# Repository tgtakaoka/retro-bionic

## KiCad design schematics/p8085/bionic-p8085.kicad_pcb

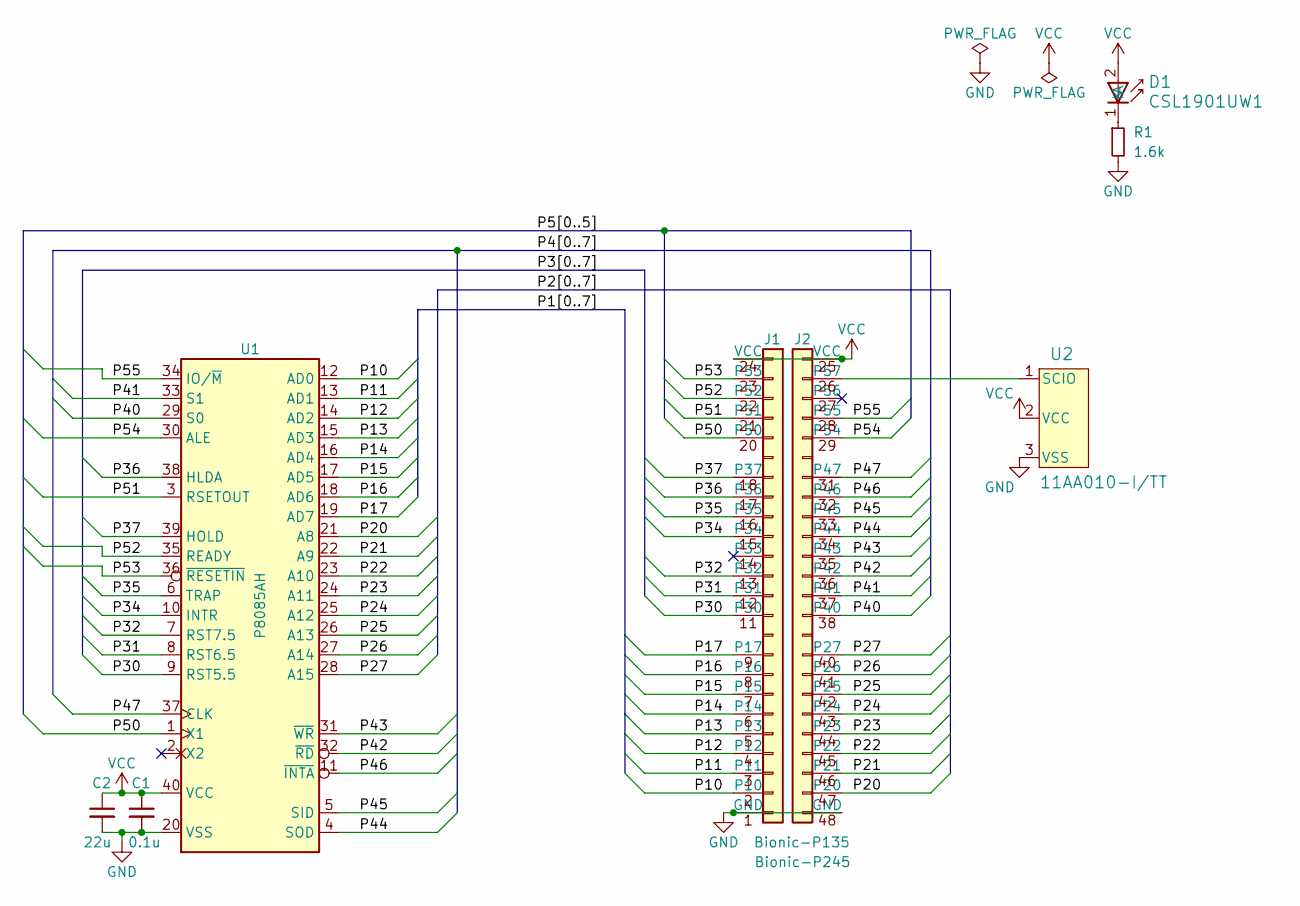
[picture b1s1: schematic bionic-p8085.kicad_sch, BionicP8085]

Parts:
C1: 0.1u; C_0603_1608Metric_Pad1.08x0.95mm_HandSolder
C2: 22u; C_0603_1608Metric_Pad1.08x0.95mm_HandSolder
D1: CSL1901UW1; LED_CSL1901UW1_ROM-M
J1: Bionic-P135; Bionic-P135_THT
J2: Bionic-P245; Bionic-P245_THT
R1: 1.6k; R_0603_1608Metric_Pad0.98x0.95mm_HandSolder
U1: P8085AH; DIP-40_W15.24mm_Socket
U2: 11AA010-I/TT; SOT-23_MC_MCH-M

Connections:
/P10: J1.2 (P10), U1.12 (AD0)
/P11: J1.3 (P11), U1.13 (AD1)
/P12: J1.4 (P12), U1.14 (AD2)
/P13: J1.5 (P13), U1.15 (AD3)
/P14: J1.6 (P14), U1.16 (AD4)
/P15: J1.7 (P15), U1.17 (AD5)
/P16: J1.8 (P16), U1.18 (AD6)
/P17: J1.9 (P17), U1.19 (AD7)
/P20: J2.47 (P20), U1.21 (A8)
/P21: J2.46 (P21), U1.22 (A9)
/P22: J2.45 (P22), U1.23 (A10)
/P23: J2.44 (P23), U1.24 (A11)
/P24: J2.43 (P24), U1.25 (A12)
/P25: J2.42 (P25), U1.26 (A13)
/P26: J2.41 (P26), U1.27 (A14)
/P27: J2.40 (P27), U1.28 (A15)
/P30: J1.11 (P30), U1.9 (RST5.5)
/P31: J1.12 (P31), U1.8 (RST6.5)
/P32: J1.13 (P32), U1.7 (RST7.5)
/P34: J1.15 (P34), U1.10 (INTR)
/P35: J1.16 (P35), U1.6 (TRAP)
/P36: J1.17 (P36), U1.38 (HLDA)
/P37: J1.18 (P37), U1.39 (HOLD)
/P40: J2.38 (P40), U1.29 (S0)
/P41: J2.37 (P41), U1.33 (S1)
/P42: J2.36 (P42), U1.32 (~RD)
/P43: J2.35 (P43), U1.31 (~WR)
/P44: J2.34 (P44), U1.4 (SOD)
/P45: J2.33 (P45), U1.5 (SID)
/P46: J2.32 (P46), U1.11 (~INTA)
/P47: J2.31 (P47), U1.37 (CLK)
/P50: J1.20 (P50), U1.1 (X1)
/P51: J1.21 (P51), U1.3 (RSETOUT)
/P52: J1.22 (P52), U1.35 (READY)
/P53: J1.23 (P53), U1.36 (~RESETIN)
/P54: J2.29 (P54), U1.30 (ALE)
/P55: J2.28 (P55), U1.34 (IO/~M)
GND: C1.2, C2.2, J1.1 (GND), J2.48 (GND), R1.2, U1.20 (VSS), U2.3 (VSS)
unnamed: D1.1 (K), R1.1
unnamed: J2.26 (P57), U2.1 (SCIO)
VCC: C1.1, C2.1, D1.2 (A), J1.24 (VCC), J2.25 (VCC), U1.40 (VCC), U2.2 (VCC)

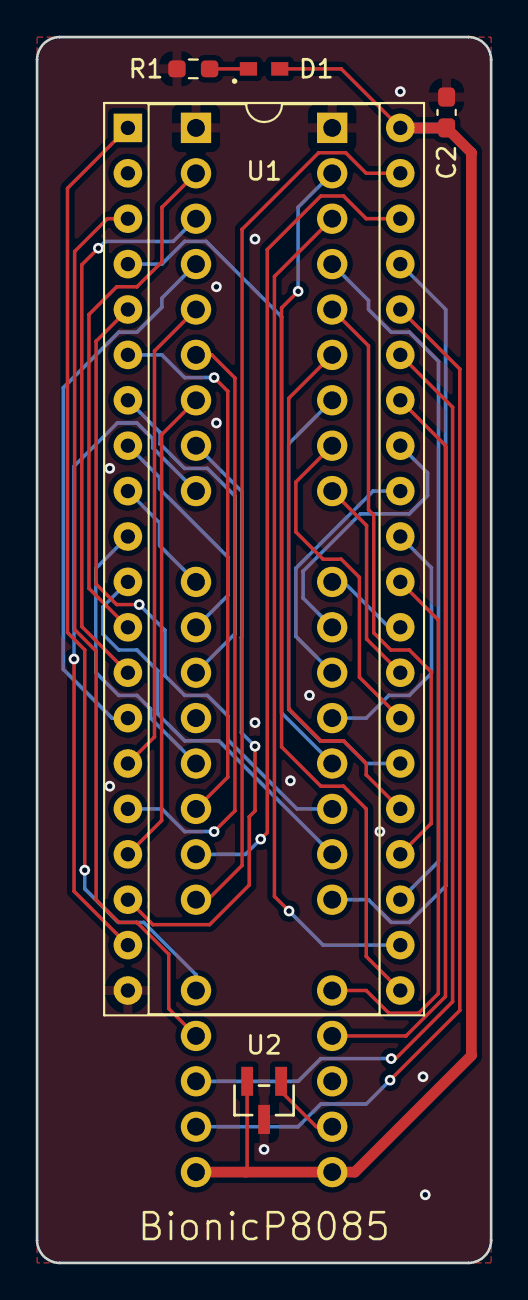
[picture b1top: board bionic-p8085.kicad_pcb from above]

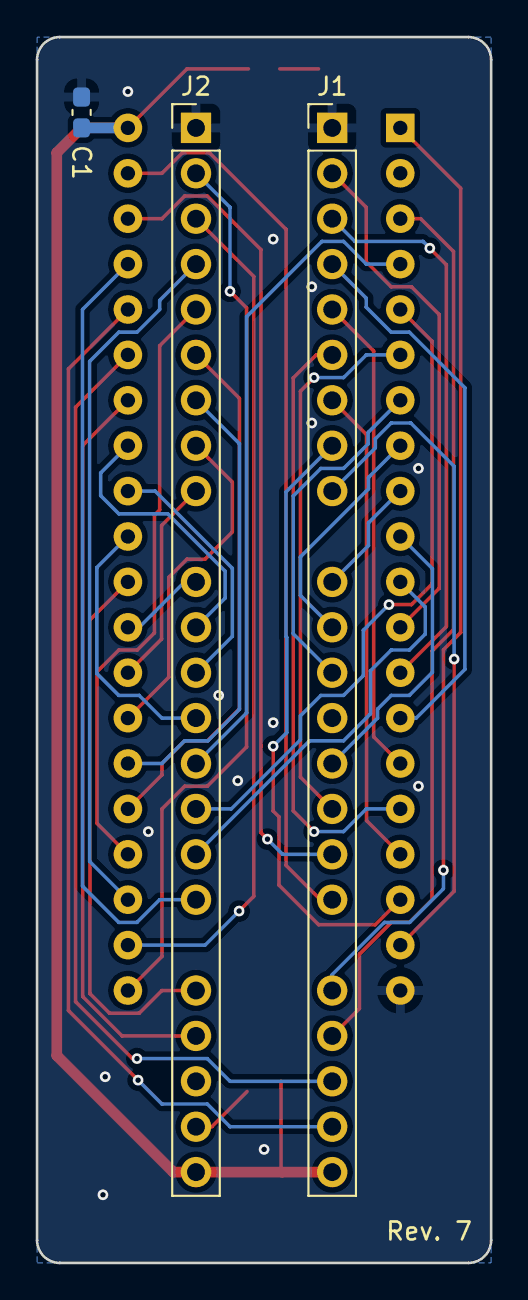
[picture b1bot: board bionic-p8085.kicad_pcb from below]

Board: 2 copper layers, 25.4 x 68.6 mm, 8 parts (3 on the bottom side), 41 nets.

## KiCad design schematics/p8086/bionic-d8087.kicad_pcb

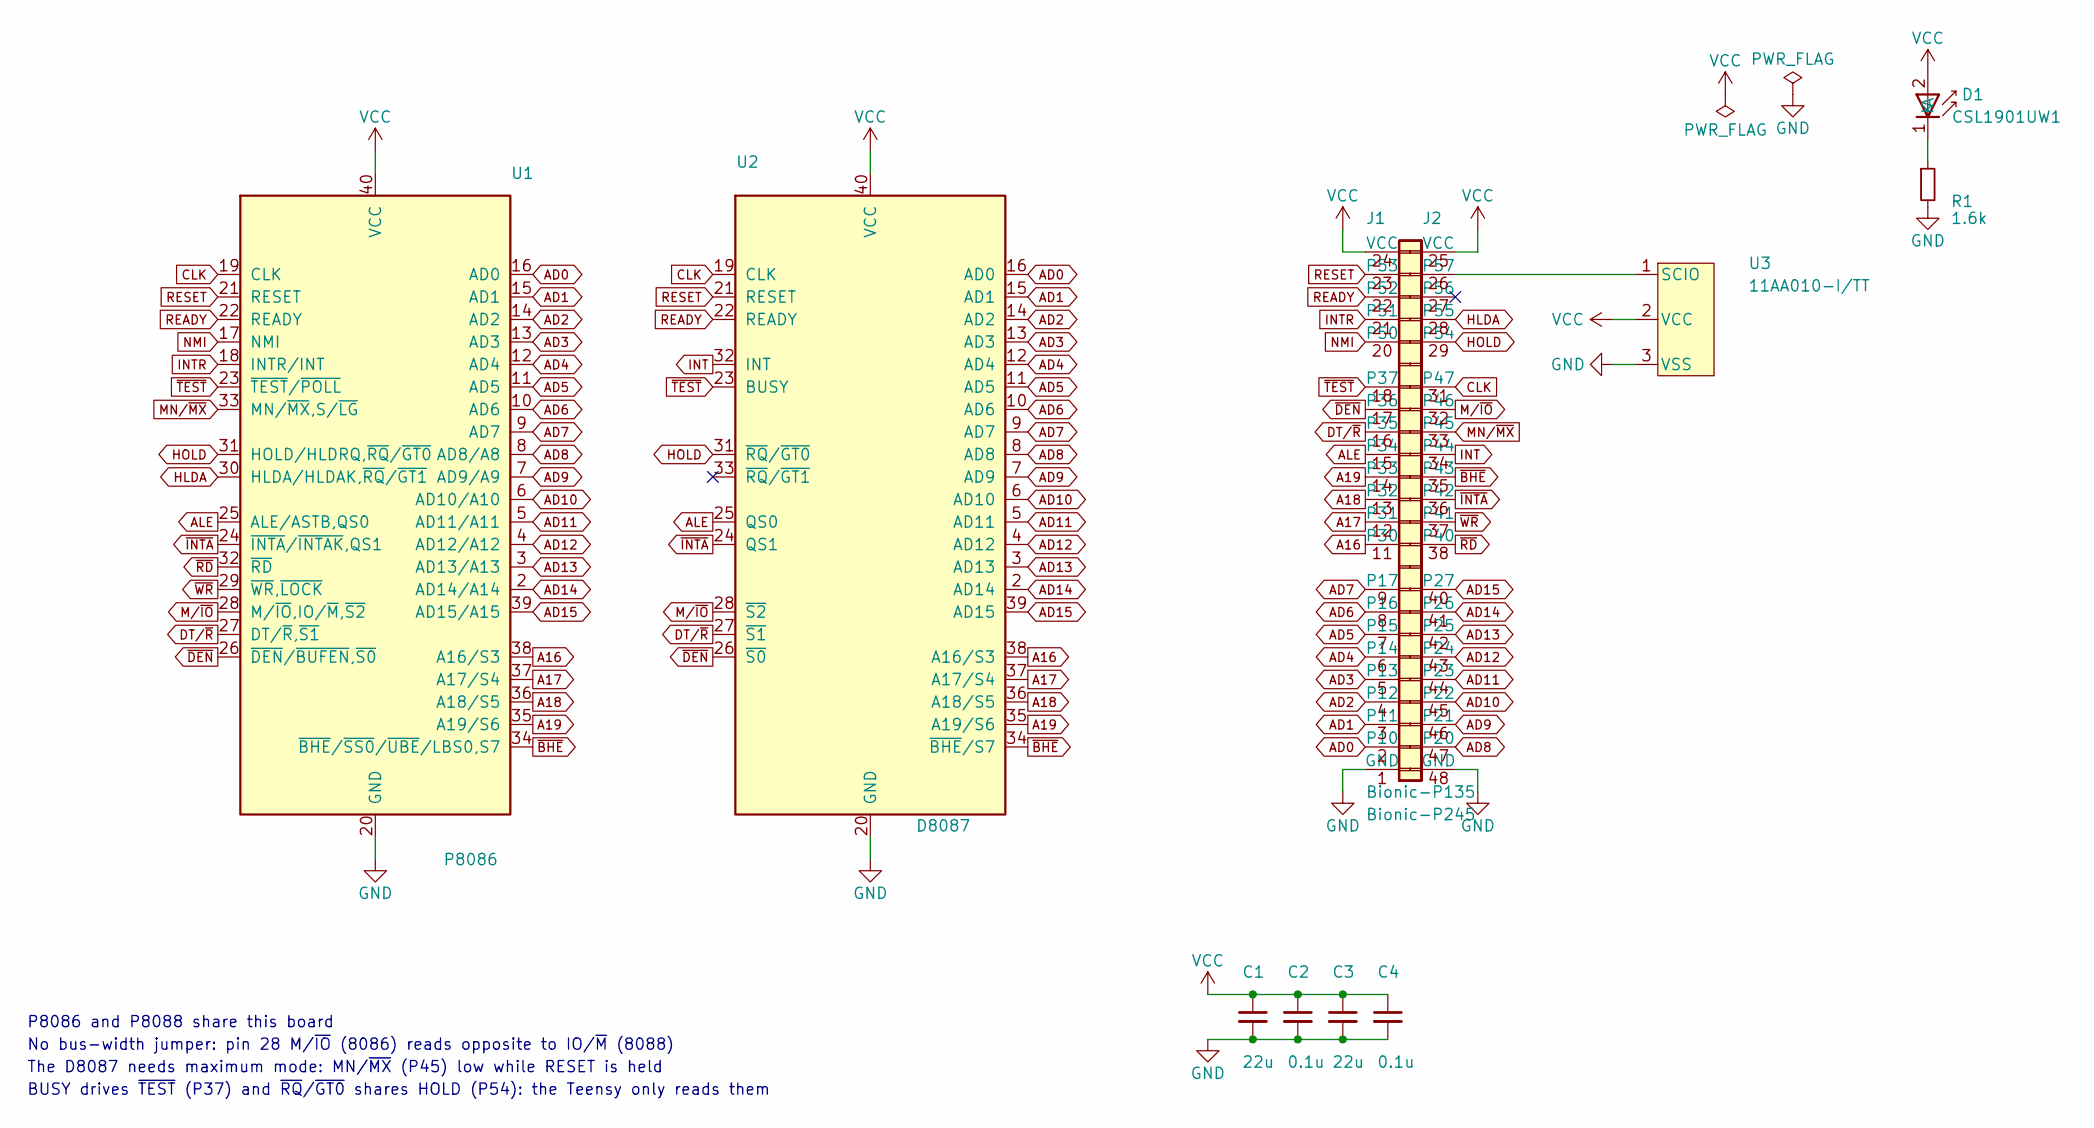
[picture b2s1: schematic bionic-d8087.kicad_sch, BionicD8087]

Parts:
C1, C3: 22u; C_0603_1608Metric_Pad1.08x0.95mm_HandSolder
C2, C4: 0.1u; C_0603_1608Metric_Pad1.08x0.95mm_HandSolder
D1: CSL1901UW1; LED_CSL1901UW1_ROM-M
J1: Bionic-P135; Bionic-P135_THT
J2: Bionic-P245; Bionic-P245_THT
R1: 1.6k; R_0603_1608Metric_Pad0.98x0.95mm_HandSolder
U1: P8086; DIP-40_W15.24mm_Socket
U2: D8087; DIP-40_W15.24mm_Socket
U3: 11AA010-I/TT; SOT-23_MC_MCH-M

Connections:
A16: J1.11 (P30), U1.38 (A16/S3), U2.38 (A16/S3)
A17: J1.12 (P31), U1.37 (A17/S4), U2.37 (A17/S4)
A18: J1.13 (P32), U1.36 (A18/S5), U2.36 (A18/S5)
A19: J1.14 (P33), U1.35 (A19/S6), U2.35 (A19/S6)
AD0: J1.2 (P10), U1.16 (AD0), U2.16 (AD0)
AD1: J1.3 (P11), U1.15 (AD1), U2.15 (AD1)
AD2: J1.4 (P12), U1.14 (AD2), U2.14 (AD2)
AD3: J1.5 (P13), U1.13 (AD3), U2.13 (AD3)
AD4: J1.6 (P14), U1.12 (AD4), U2.12 (AD4)
AD5: J1.7 (P15), U1.11 (AD5), U2.11 (AD5)
AD6: J1.8 (P16), U1.10 (AD6), U2.10 (AD6)
AD7: J1.9 (P17), U1.9 (AD7), U2.9 (AD7)
AD8: J2.47 (P20), U1.8 (AD8/A8), U2.8 (AD8)
AD9: J2.46 (P21), U1.7 (AD9/A9), U2.7 (AD9)
AD10: J2.45 (P22), U1.6 (AD10/A10), U2.6 (AD10)
AD11: J2.44 (P23), U1.5 (AD11/A11), U2.5 (AD11)
AD12: J2.43 (P24), U1.4 (AD12/A12), U2.4 (AD12)
AD13: J2.42 (P25), U1.3 (AD13/A13), U2.3 (AD13)
AD14: J2.41 (P26), U1.2 (AD14/A14), U2.2 (AD14)
AD15: J2.40 (P27), U1.39 (AD15/A15), U2.39 (AD15)
ALE: J1.15 (P34), U1.25 (ALE/ASTB,QS0), U2.25 (QS0)
CLK: J2.31 (P47), U1.19 (CLK), U2.19 (CLK)
DT/~R: J1.16 (P35), U1.27 (DT/~R,~S1), U2.27 (~S1)
GND: C1.2, C2.2, C3.2, C4.2, J1.1 (GND), J2.48 (GND), R1.2, U1.1 (GND), U1.20 (GND), U2.1 (GND), U2.20 (GND), U3.3 (VSS)
HLDA: J2.28 (P55), U1.30 (HLDA/HLDAK,~RQ/~GT1)
HOLD: J2.29 (P54), U1.31 (HOLD/HLDRQ,~RQ/~GT0), U2.31 (~RQ/~GT0)
INT: J2.34 (P44), U2.32 (INT)
INTR: J1.21 (P51), U1.18 (INTR/INT)
MN/~MX: J2.33 (P45), U1.33 (MN/~MX,S/~LG)
M/~IO: J2.32 (P46), U1.28 (M/~IO,IO/~M,~S2), U2.28 (~S2)
NMI: J1.20 (P50), U1.17 (NMI)
unnamed: D1.1 (K), R1.1
unnamed: J2.26 (P57), U3.1 (SCIO)
READY: J1.22 (P52), U1.22 (READY), U2.22 (READY)
RESET: J1.23 (P53), U1.21 (RESET), U2.21 (RESET)
VCC: C1.1, C2.1, C3.1, C4.1, D1.2 (A), J1.24 (VCC), J2.25 (VCC), U1.40 (VCC), U2.40 (VCC), U3.2 (VCC)
~BHE: J2.35 (P43), U1.34 (~BHE/~SS0/~UBE/LBS0,S7), U2.34 (~BHE/S7)
~DEN: J1.17 (P36), U1.26 (~DEN/~BUFEN,~S0), U2.26 (~S0)
~INTA: J2.36 (P42), U1.24 (~INTA/~INTAK,QS1), U2.24 (QS1)
~RD: J2.38 (P40), U1.32 (~RD)
~TEST: J1.18 (P37), U1.23 (~TEST/~POLL), U2.23 (BUSY)
~WR: J2.37 (P41), U1.29 (~WR,~LOCK)

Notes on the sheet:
P8086 and P8088 share this board
The D8087 needs maximum mode: MN/~{MX} (P45) low while RESET is held
No bus-width jumper: pin 28 M/~{IO} (8086) reads opposite to IO/~{M} (8088)
BUSY drives ~{TEST} (P37) and ~{RQ}/~{GT0} shares HOLD (P54): the Teensy only reads them

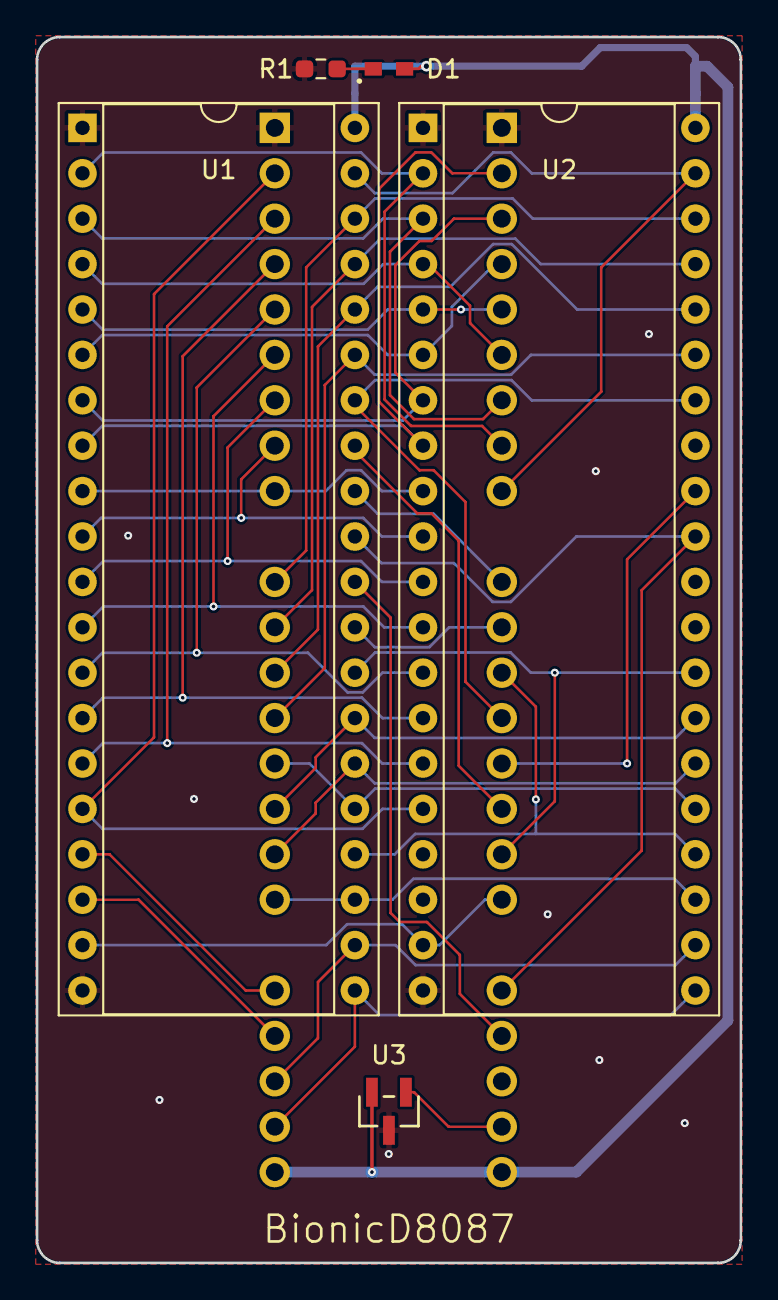
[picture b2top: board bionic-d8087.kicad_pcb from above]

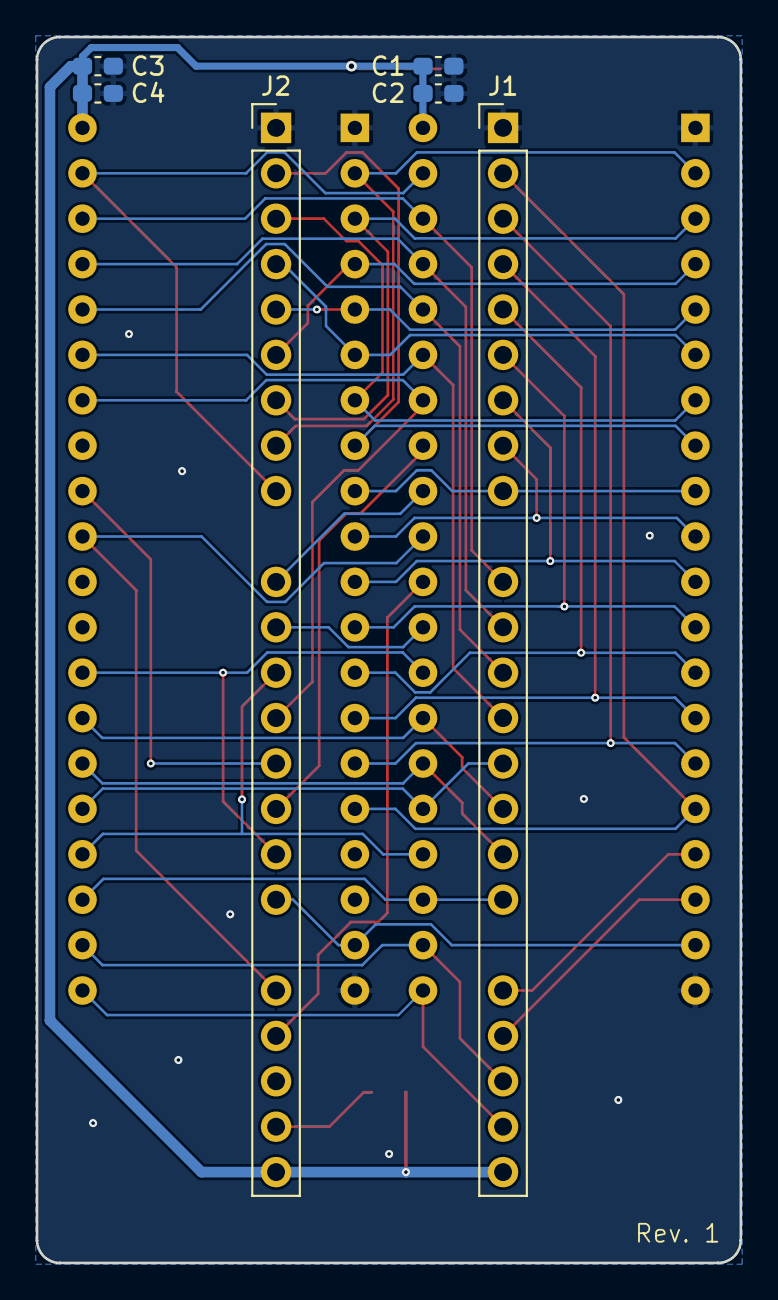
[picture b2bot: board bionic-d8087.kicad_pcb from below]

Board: 2 copper layers, 39.4 x 68.6 mm, 11 parts (6 on the bottom side), 42 nets.

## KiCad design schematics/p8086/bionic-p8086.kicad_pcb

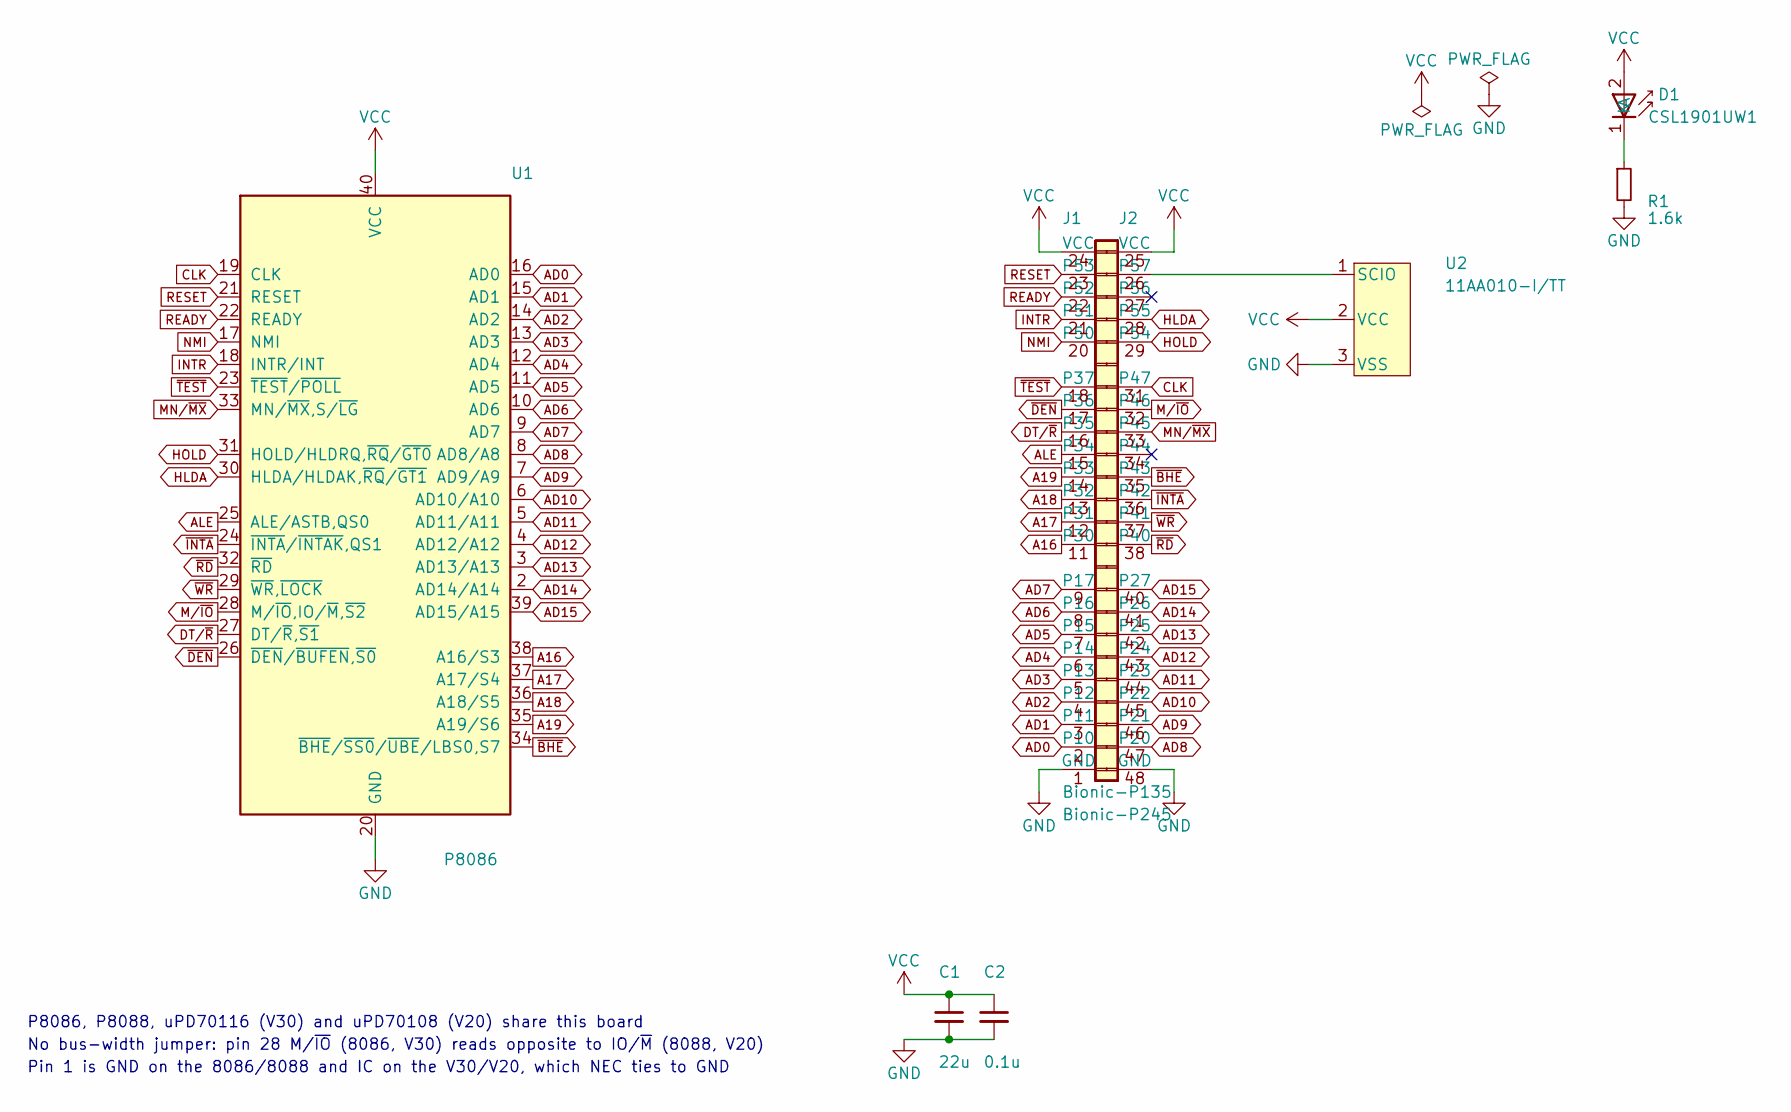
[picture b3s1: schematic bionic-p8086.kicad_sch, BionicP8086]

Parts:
C1: 22u; C_0603_1608Metric_Pad1.08x0.95mm_HandSolder
C2: 0.1u; C_0603_1608Metric_Pad1.08x0.95mm_HandSolder
D1: CSL1901UW1; LED_CSL1901UW1_ROM-M
J1: Bionic-P135; Bionic-P135_THT
J2: Bionic-P245; Bionic-P245_THT
R1: 1.6k; R_0603_1608Metric_Pad0.98x0.95mm_HandSolder
U1: P8086; DIP-40_W15.24mm_Socket
U2: 11AA010-I/TT; SOT-23_MC_MCH-M

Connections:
A16: J1.11 (P30), U1.38 (A16/S3)
A17: J1.12 (P31), U1.37 (A17/S4)
A18: J1.13 (P32), U1.36 (A18/S5)
A19: J1.14 (P33), U1.35 (A19/S6)
AD0: J1.2 (P10), U1.16 (AD0)
AD1: J1.3 (P11), U1.15 (AD1)
AD2: J1.4 (P12), U1.14 (AD2)
AD3: J1.5 (P13), U1.13 (AD3)
AD4: J1.6 (P14), U1.12 (AD4)
AD5: J1.7 (P15), U1.11 (AD5)
AD6: J1.8 (P16), U1.10 (AD6)
AD7: J1.9 (P17), U1.9 (AD7)
AD8: J2.47 (P20), U1.8 (AD8/A8)
AD9: J2.46 (P21), U1.7 (AD9/A9)
AD10: J2.45 (P22), U1.6 (AD10/A10)
AD11: J2.44 (P23), U1.5 (AD11/A11)
AD12: J2.43 (P24), U1.4 (AD12/A12)
AD13: J2.42 (P25), U1.3 (AD13/A13)
AD14: J2.41 (P26), U1.2 (AD14/A14)
AD15: J2.40 (P27), U1.39 (AD15/A15)
ALE: J1.15 (P34), U1.25 (ALE/ASTB,QS0)
CLK: J2.31 (P47), U1.19 (CLK)
DT/~R: J1.16 (P35), U1.27 (DT/~R,~S1)
GND: C1.2, C2.2, J1.1 (GND), J2.48 (GND), R1.2, U1.1 (GND), U1.20 (GND), U2.3 (VSS)
HLDA: J2.28 (P55), U1.30 (HLDA/HLDAK,~RQ/~GT1)
HOLD: J2.29 (P54), U1.31 (HOLD/HLDRQ,~RQ/~GT0)
INTR: J1.21 (P51), U1.18 (INTR/INT)
MN/~MX: J2.33 (P45), U1.33 (MN/~MX,S/~LG)
M/~IO: J2.32 (P46), U1.28 (M/~IO,IO/~M,~S2)
NMI: J1.20 (P50), U1.17 (NMI)
unnamed: D1.1 (K), R1.1
unnamed: J2.26 (P57), U2.1 (SCIO)
READY: J1.22 (P52), U1.22 (READY)
RESET: J1.23 (P53), U1.21 (RESET)
VCC: C1.1, C2.1, D1.2 (A), J1.24 (VCC), J2.25 (VCC), U1.40 (VCC), U2.2 (VCC)
~BHE: J2.35 (P43), U1.34 (~BHE/~SS0/~UBE/LBS0,S7)
~DEN: J1.17 (P36), U1.26 (~DEN/~BUFEN,~S0)
~INTA: J2.36 (P42), U1.24 (~INTA/~INTAK,QS1)
~RD: J2.38 (P40), U1.32 (~RD)
~TEST: J1.18 (P37), U1.23 (~TEST/~POLL)
~WR: J2.37 (P41), U1.29 (~WR,~LOCK)

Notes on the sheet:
P8086, P8088, uPD70116 (V30) and uPD70108 (V20) share this board
No bus-width jumper: pin 28 M/~{IO} (8086, V30) reads opposite to IO/~{M} (8088, V20)
Pin 1 is GND on the 8086/8088 and IC on the V30/V20, which NEC ties to GND

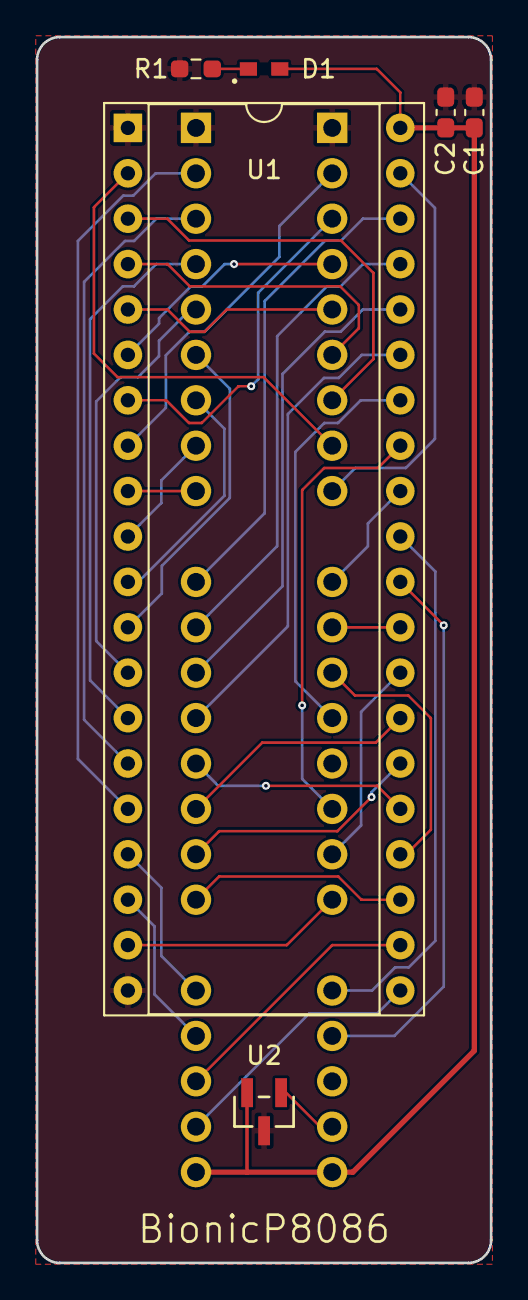
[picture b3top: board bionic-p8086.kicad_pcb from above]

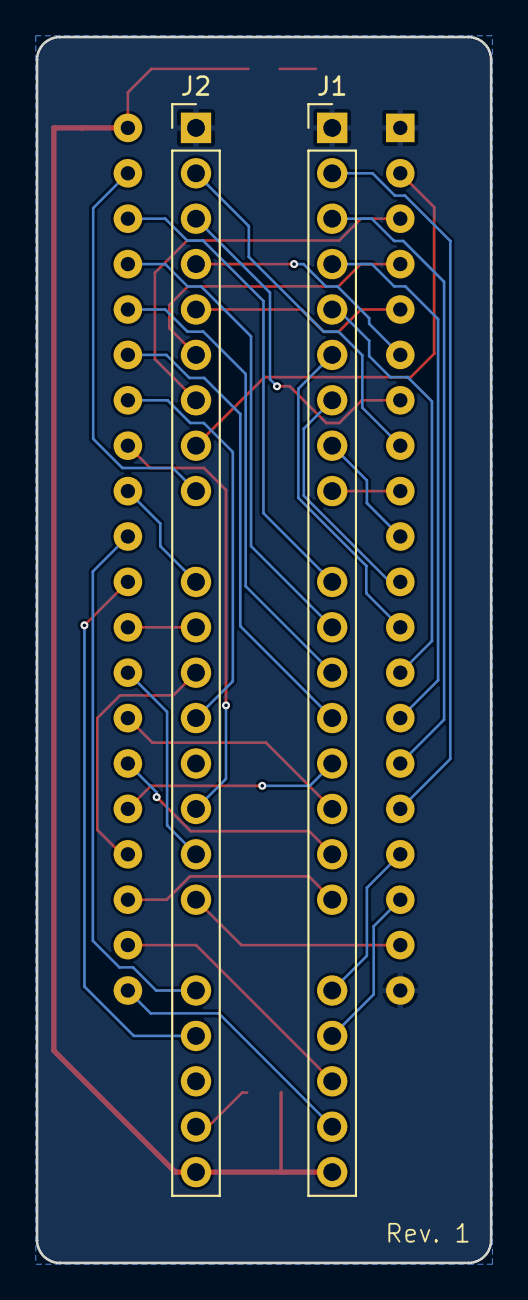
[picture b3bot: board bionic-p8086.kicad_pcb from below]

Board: 2 copper layers, 25.4 x 68.6 mm, 8 parts (2 on the bottom side), 41 nets.

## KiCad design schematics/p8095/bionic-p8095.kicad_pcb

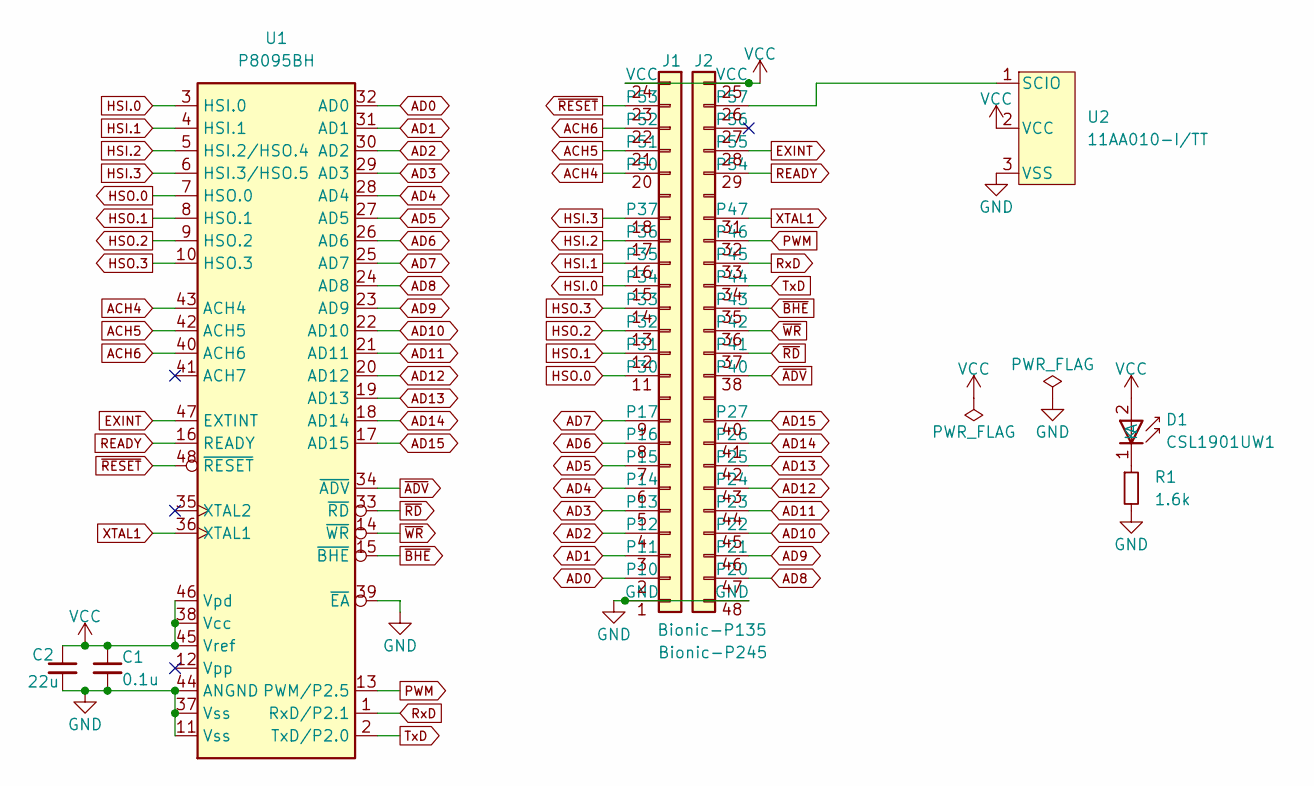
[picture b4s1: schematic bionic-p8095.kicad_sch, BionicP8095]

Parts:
C1: 0.1u; C_0603_1608Metric_Pad1.08x0.95mm_HandSolder
C2: 22u; C_0603_1608Metric_Pad1.08x0.95mm_HandSolder
D1: CSL1901UW1; LED_CSL1901UW1_ROM-M
J1: Bionic-P135; Bionic-P135_THT
J2: Bionic-P245; Bionic-P245_THT
R1: 1.6k; R_0603_1608Metric_Pad0.98x0.95mm_HandSolder
U1: P8095BH; DIP-48_W15.24mm_Socket
U2: 11AA010-I/TT; SOT-23_MC_MCH-M

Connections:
ACH4: J1.20 (P50), U1.43 (ACH4)
ACH5: J1.21 (P51), U1.42 (ACH5)
ACH6: J1.22 (P52), U1.40 (ACH6)
AD0: J1.2 (P10), U1.32 (AD0)
AD1: J1.3 (P11), U1.31 (AD1)
AD2: J1.4 (P12), U1.30 (AD2)
AD3: J1.5 (P13), U1.29 (AD3)
AD4: J1.6 (P14), U1.28 (AD4)
AD5: J1.7 (P15), U1.27 (AD5)
AD6: J1.8 (P16), U1.26 (AD6)
AD7: J1.9 (P17), U1.25 (AD7)
AD8: J2.47 (P20), U1.24 (AD8)
AD9: J2.46 (P21), U1.23 (AD9)
AD10: J2.45 (P22), U1.22 (AD10)
AD11: J2.44 (P23), U1.21 (AD11)
AD12: J2.43 (P24), U1.20 (AD12)
AD13: J2.42 (P25), U1.19 (AD13)
AD14: J2.41 (P26), U1.18 (AD14)
AD15: J2.40 (P27), U1.17 (AD15)
EXINT: J2.28 (P55), U1.47 (EXTINT)
GND: C1.2, C2.2, J1.1 (GND), J2.48 (GND), R1.2, U1.11 (Vss), U1.37 (Vss), U1.39 (~EA), U1.44 (ANGND), U2.3 (VSS)
HSI.0: J1.15 (P34), U1.3 (HSI.0)
HSI.1: J1.16 (P35), U1.4 (HSI.1)
HSI.2: J1.17 (P36), U1.5 (HSI.2/HSO.4)
HSI.3: J1.18 (P37), U1.6 (HSI.3/HSO.5)
HSO.0: J1.11 (P30), U1.7 (HSO.0)
HSO.1: J1.12 (P31), U1.8 (HSO.1)
HSO.2: J1.13 (P32), U1.9 (HSO.2)
HSO.3: J1.14 (P33), U1.10 (HSO.3)
unnamed: D1.1 (K), R1.1
unnamed: J2.26 (P57), U2.1 (SCIO)
PWM: J2.32 (P46), U1.13 (PWM/P2.5)
READY: J2.29 (P54), U1.16 (READY)
RxD: J2.33 (P45), U1.1 (RxD/P2.1)
TxD: J2.34 (P44), U1.2 (TxD/P2.0)
VCC: C1.1, C2.1, D1.2 (A), J1.24 (VCC), J2.25 (VCC), U1.38 (Vcc), U1.45 (Vref), U1.46 (Vpd), U2.2 (VCC)
XTAL1: J2.31 (P47), U1.36 (XTAL1)
~ADV: J2.38 (P40), U1.34 (~ADV)
~BHE: J2.35 (P43), U1.15 (~BHE)
~RD: J2.37 (P41), U1.33 (~RD)
~RESET: J1.23 (P53), U1.48 (~RESET)
~WR: J2.36 (P42), U1.14 (~WR)

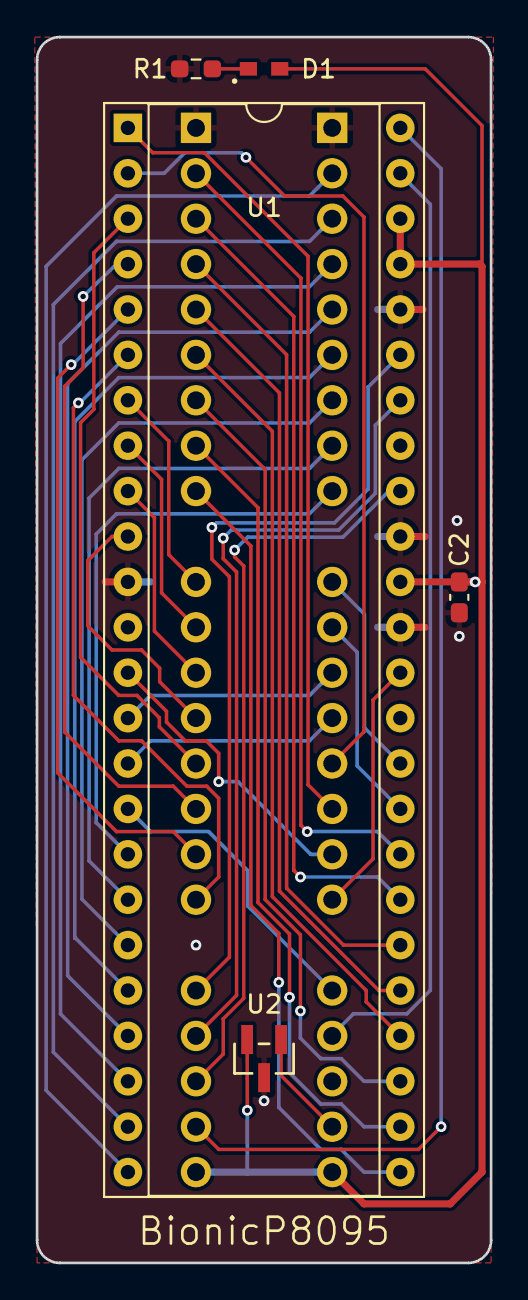
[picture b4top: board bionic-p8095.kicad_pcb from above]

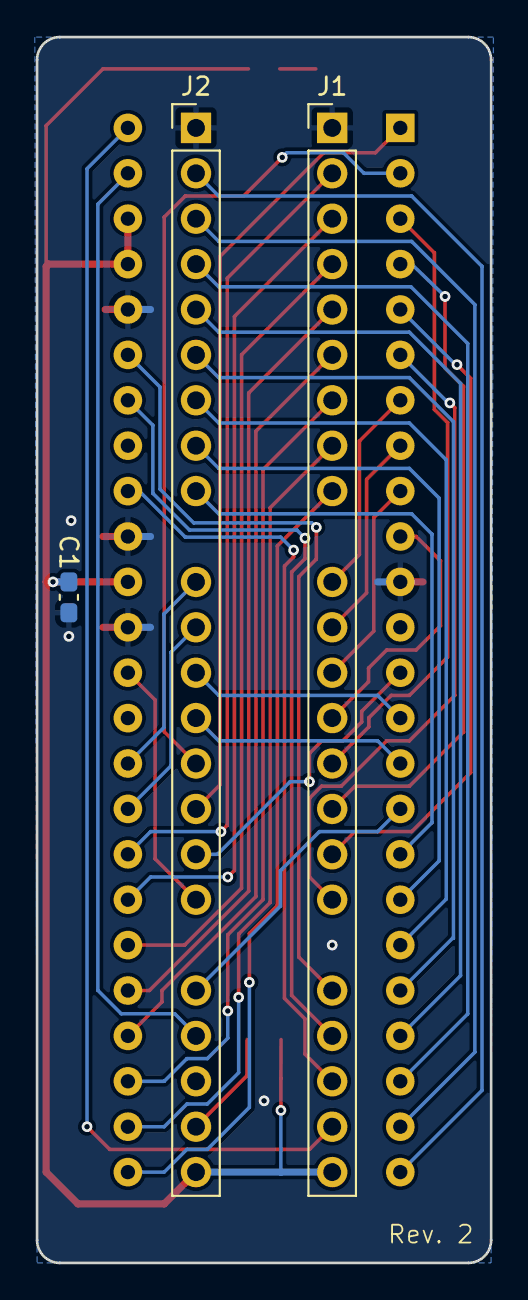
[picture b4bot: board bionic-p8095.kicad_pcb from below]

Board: 2 copper layers, 25.4 x 68.6 mm, 8 parts (3 on the bottom side), 42 nets.

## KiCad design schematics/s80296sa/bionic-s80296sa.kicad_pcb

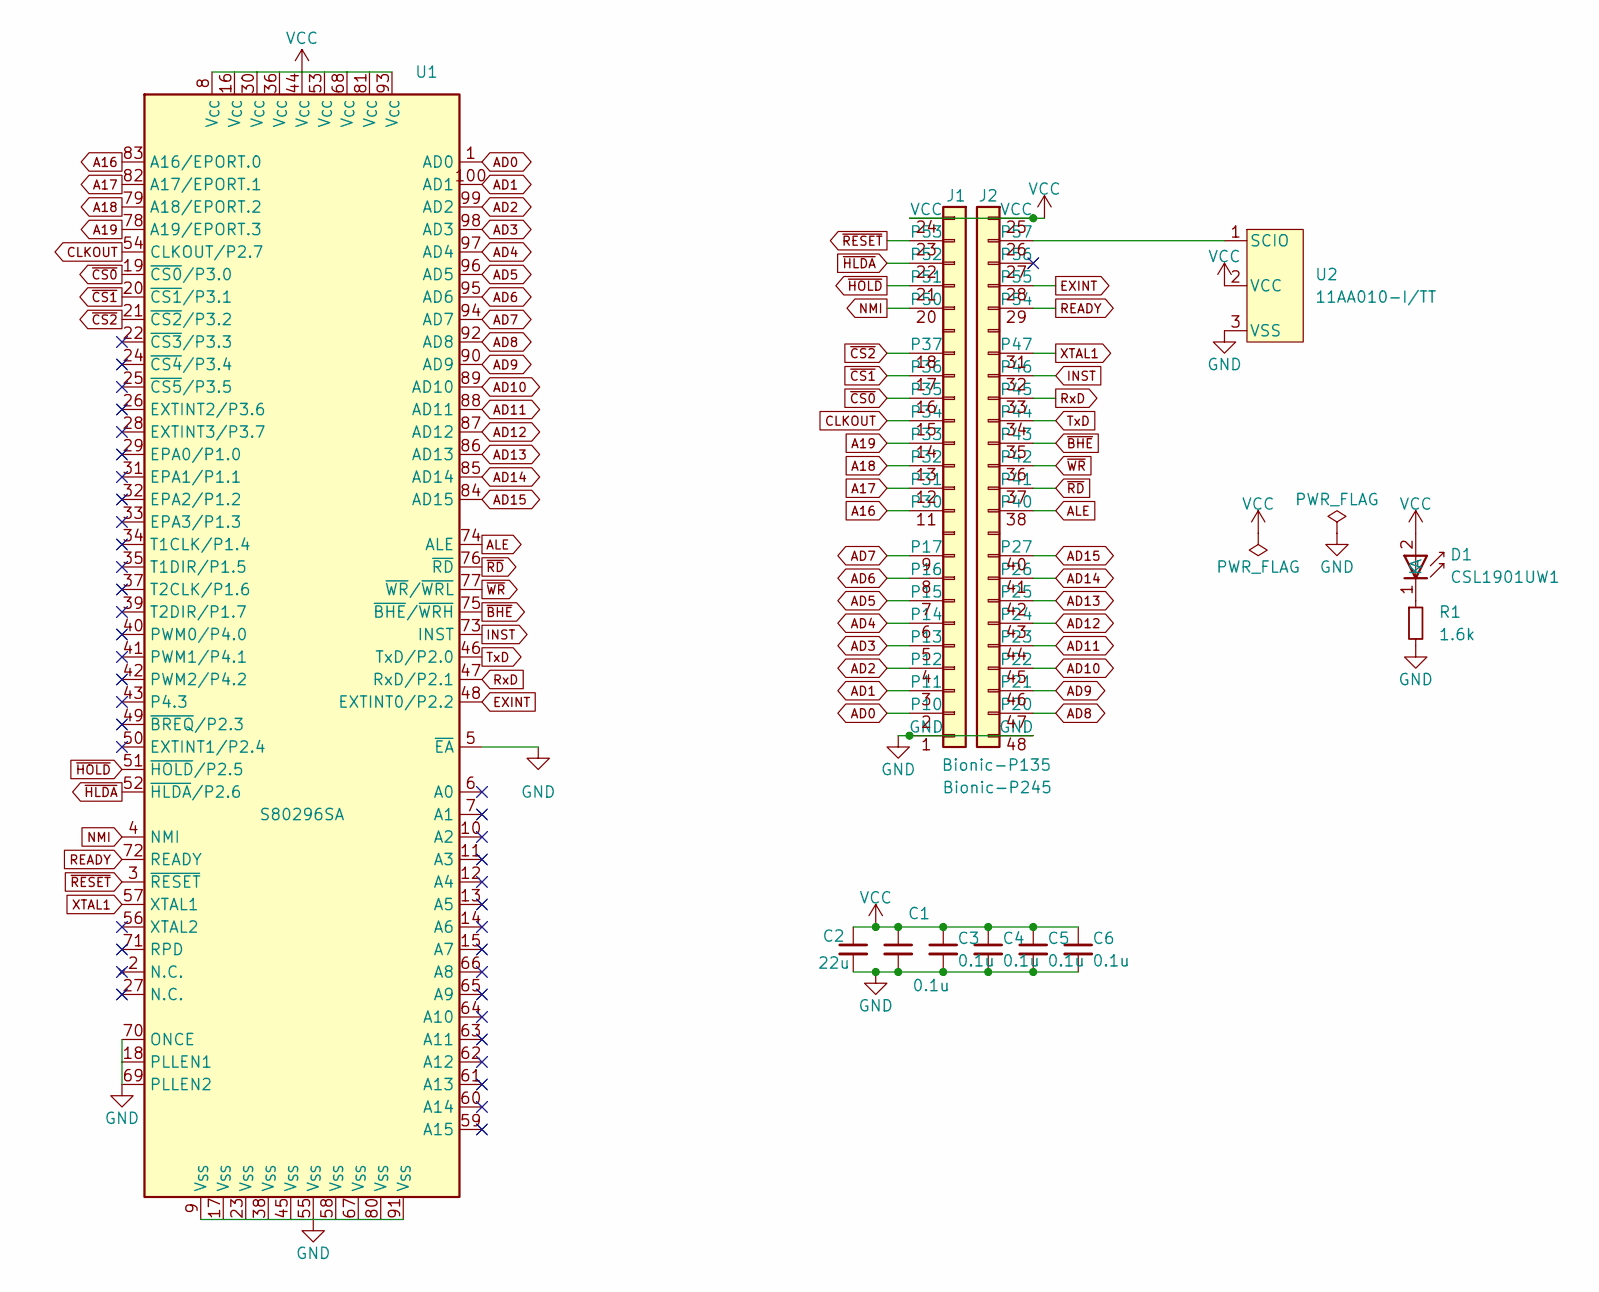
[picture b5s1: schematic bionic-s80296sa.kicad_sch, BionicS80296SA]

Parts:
C1, C3, C4, C5, C6: 0.1u; C_0603_1608Metric_Pad1.08x0.95mm_HandSolder
C2: 22u; C_0603_1608Metric_Pad1.08x0.95mm_HandSolder
D1: CSL1901UW1; LED_CSL1901UW1_ROM-M
J1: Bionic-P135; Bionic-P135_SMT
J2: Bionic-P245; Bionic-P245_SMT
R1: 1.6k; R_0603_1608Metric_Pad0.98x0.95mm_HandSolder
U1: S80296SA; PQFP-100_14x20mm_P0.65mm_Intel
U2: 11AA010-I/TT; SOT-23_MC_MCH-M

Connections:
A16: J1.11 (P30), U1.83 (A16/EPORT.0)
A17: J1.12 (P31), U1.82 (A17/EPORT.1)
A18: J1.13 (P32), U1.79 (A18/EPORT.2)
A19: J1.14 (P33), U1.78 (A19/EPORT.3)
AD0: J1.2 (P10), U1.1 (AD0)
AD1: J1.3 (P11), U1.100 (AD1)
AD2: J1.4 (P12), U1.99 (AD2)
AD3: J1.5 (P13), U1.98 (AD3)
AD4: J1.6 (P14), U1.97 (AD4)
AD5: J1.7 (P15), U1.96 (AD5)
AD6: J1.8 (P16), U1.95 (AD6)
AD7: J1.9 (P17), U1.94 (AD7)
AD8: J2.47 (P20), U1.92 (AD8)
AD9: J2.46 (P21), U1.90 (AD9)
AD10: J2.45 (P22), U1.89 (AD10)
AD11: J2.44 (P23), U1.88 (AD11)
AD12: J2.43 (P24), U1.87 (AD12)
AD13: J2.42 (P25), U1.86 (AD13)
AD14: J2.41 (P26), U1.85 (AD14)
AD15: J2.40 (P27), U1.84 (AD15)
ALE: J2.38 (P40), U1.74 (ALE)
CLKOUT: J1.15 (P34), U1.54 (CLKOUT/P2.7)
EXINT: J2.28 (P55), U1.48 (EXTINT0/P2.2)
GND: C1.2, C2.2, C3.2, C4.2, C5.2, C6.2, J1.1 (GND), J2.48 (GND), R1.2, U1.5 (~EA), U1.9 (V_{SS}), U1.17 (V_{SS}), U1.18 (PLLEN1), U1.23 (V_{SS}), U1.38 (V_{SS}), U1.45 (V_{SS}), U1.55 (V_{SS}), U1.58 (V_{SS}), U1.67 (V_{SS}), U1.69 (PLLEN2), U1.70 (ONCE), U1.80 (V_{SS}), U1.91 (V_{SS}), U2.3 (VSS)
INST: J2.32 (P46), U1.73 (INST)
NMI: J1.20 (P50), U1.4 (NMI)
unnamed: D1.1 (K), R1.1
unnamed: J2.26 (P57), U2.1 (SCIO)
READY: J2.29 (P54), U1.72 (READY)
RxD: J2.33 (P45), U1.47 (RxD/P2.1)
TxD: J2.34 (P44), U1.46 (TxD/P2.0)
VCC: C1.1, C2.1, C3.1, C4.1, C5.1, C6.1, D1.2 (A), J1.24 (VCC), J2.25 (VCC), U1.8 (V_{CC}), U1.16 (V_{CC}), U1.30 (V_{CC}), U1.36 (V_{CC}), U1.44 (V_{CC}), U1.53 (V_{CC}), U1.68 (V_{CC}), U1.81 (V_{CC}), U1.93 (V_{CC}), U2.2 (VCC)
XTAL1: J2.31 (P47), U1.57 (XTAL1)
~BHE: J2.35 (P43), U1.75 (~BHE/~WRH)
~CS0: J1.16 (P35), U1.19 (~CS0/P3.0)
~CS1: J1.17 (P36), U1.20 (~CS1/P3.1)
~CS2: J1.18 (P37), U1.21 (~CS2/P3.2)
~HLDA: J1.22 (P52), U1.52 (~HLDA/P2.6)
~HOLD: J1.21 (P51), U1.51 (~HOLD/P2.5)
~RD: J2.37 (P41), U1.76 (~RD)
~RESET: J1.23 (P53), U1.3 (~RESET)
~WR: J2.36 (P42), U1.77 (~WR/~WRL)
